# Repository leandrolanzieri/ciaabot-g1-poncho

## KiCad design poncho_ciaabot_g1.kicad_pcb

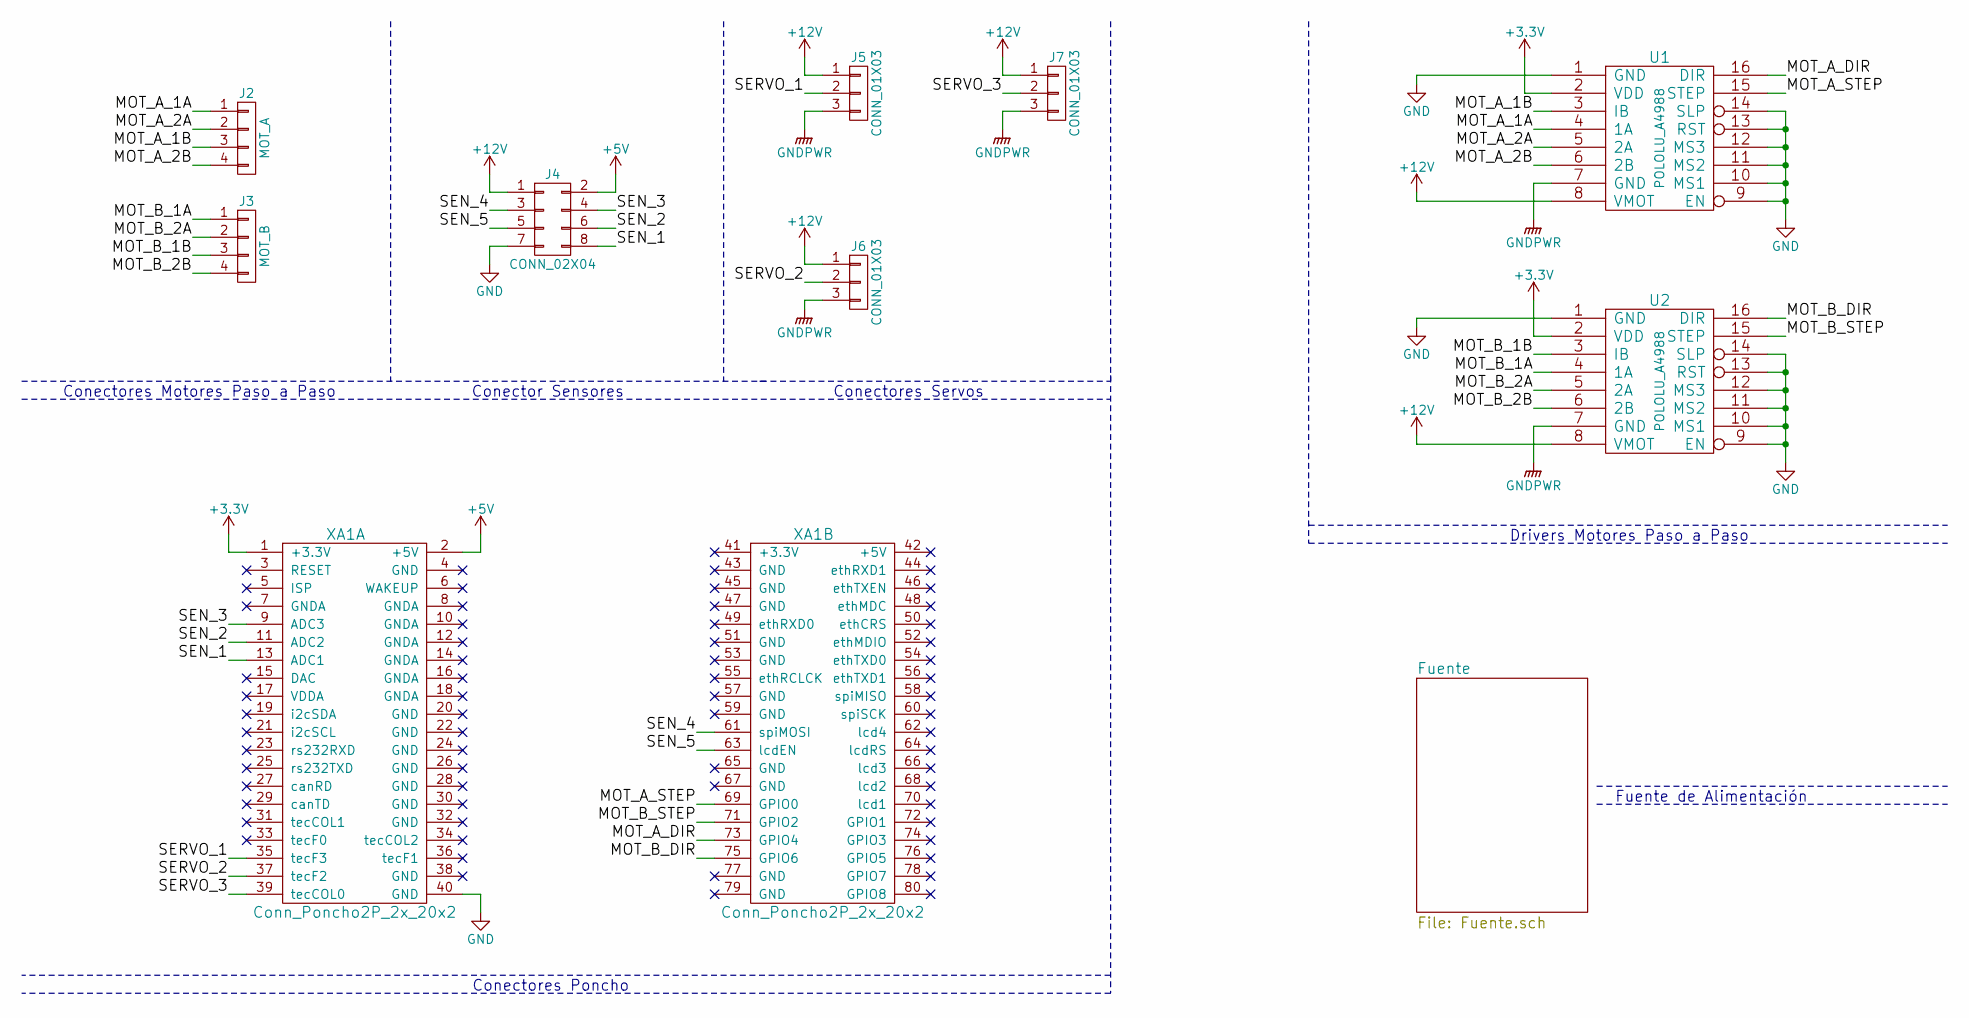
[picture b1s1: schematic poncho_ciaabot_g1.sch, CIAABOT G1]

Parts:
J2: MOT_A; Pin_Header_Straight_1x04_Pitch2.54mm; Digikey# S7002-ND
J3: MOT_B; Pin_Header_Straight_1x04_Pitch2.54mm; Digikey# S7002-ND
J4: CONN_02X04; Pin_Header_Straight_2x04_Pitch2.54mm; Digikey# S7072-ND
J5, J6, J7: CONN_01X03; Pin_Header_Straight_1x03_Pitch2.54mm; Digikey# S7001-ND
U1, U2: POLOLU_A4988; SWDIP8_.6W
XA1: Conn_Poncho2P_2x_20x2; Conn_Poncho_Completo; Digikey# 952-1897-ND

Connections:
+3V3: U1.2 (VDD), U2.2 (VDD), XA1.1 (+3.3V)
+5V: J4.2, XA1.2 (+5V)
+12V: J4.1, J5.1, J6.1, J7.1, U1.8 (VMOT), U2.8 (VMOT); also elsewhere on the board
/MOT_A_1A: J2.1, U1.4 (1A)
/MOT_A_1B: J2.3, U1.3 (IB)
/MOT_A_2A: J2.2, U1.5 (2A)
/MOT_A_2B: J2.4, U1.6 (2B)
/MOT_A_DIR: U1.16 (DIR), XA1.73 (GPIO4)
/MOT_A_STEP: U1.15 (STEP), XA1.69 (GPIO0)
/MOT_B_1A: J3.1, U2.4 (1A)
/MOT_B_1B: J3.3, U2.3 (IB)
/MOT_B_2A: J3.2, U2.5 (2A)
/MOT_B_2B: J3.4, U2.6 (2B)
/MOT_B_DIR: U2.16 (DIR), XA1.75 (GPIO6)
/MOT_B_STEP: U2.15 (STEP), XA1.71 (GPIO2)
/SEN_1: J4.8, XA1.13 (ADC1)
/SEN_2: J4.6, XA1.11 (ADC2)
/SEN_3: J4.4, XA1.9 (ADC3)
/SEN_4: J4.3, XA1.61 (spiMOSI)
/SEN_5: J4.5, XA1.63 (lcdEN)
/SERVO_1: J5.2, XA1.35 (tecF3)
/SERVO_2: J6.2, XA1.37 (tecF2)
/SERVO_3: J7.2, XA1.39 (tecCOL0)
GND: J4.7, J5.3, J6.3, J7.3, U1.1 (GND), U1.7 (GND), U1.9 (EN), U1.10 (MS1), U1.11 (MS2), U1.12 (MS3), U1.13 (RST), U1.14 (SLP), U2.1 (GND), U2.7 (GND), U2.9 (EN), U2.10 (MS1), U2.11 (MS2), U2.12 (MS3), U2.13 (RST), U2.14 (SLP), XA1.40 (GND); also elsewhere on the board

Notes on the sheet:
Conector Sensores
Conectores Servos
Drivers Motores Paso a Paso
Conectores Motores Paso a Paso
Conectores Poncho
Fuente de Alimentación

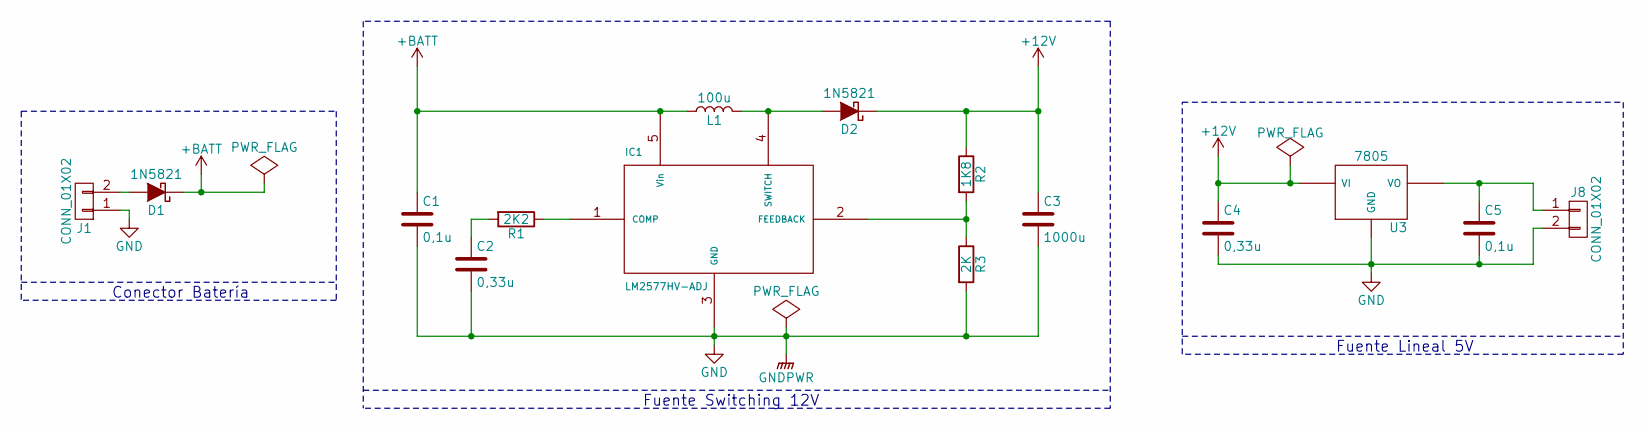
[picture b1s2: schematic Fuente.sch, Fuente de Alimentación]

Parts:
C1, C5: 0,1u; C_Disc_D3.0mm_W2.0mm_P2.50mm; Digikey# 493-10498-3-ND
C2, C4: 0,33u; C_Disc_D3.0mm_W2.0mm_P2.50mm; Digikey# 493-10258-3-ND
C3: 1000u; C_Disc_D3.0mm_W2.0mm_P2.50mm; Digikey# 1189-1583-3-ND
D1, D2: 1N5821; D_A-405_P7.62mm_Horizontal; Digikey# 1N5821FSCT-ND
IC1: LM2577HV-ADJ; TO-220-5_Vertical; Digikey# LM2577T-ADJ/NOPB-ND
J1: CONN_01X02; bornier2; Digikey# 277-1667-ND
J8: CONN_01X02; Pin_Header_Straight_2x01_Pitch2.54mm; Digikey# A1921-ND
L1: 100u; Choke_Toroid_horizontal_Diameter3-5mm_Amidon-T12; Digikey# M8354-ND
R1: 2K2; R_Axial_DIN0204_L3.6mm_D1.6mm_P5.08mm_Horizontal; Digikey# S2.2KQTR-ND
R2: 1K8; R_Axial_DIN0204_L3.6mm_D1.6mm_P5.08mm_Horizontal; Digikey# S1.8KQTR-ND
R3: 2K; R_Axial_DIN0204_L3.6mm_D1.6mm_P5.08mm_Horizontal; Digikey# S2KQTR-ND
U3: 7805; TO-220-3_Vertical; Digikey# LM7805CT-ND

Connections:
+12V: C3.1, C4.1, D2.1 (K), R2.1, U3.VI; also elsewhere on the board
+BATT: C1.1, D1.1 (K), IC1.5 (Vin), L1.1
GND: C1.2, C2.2, C3.2, C4.2, C5.2, IC1.3 (GND), J1.1, J8.2, R3.2, U3.GND; also elsewhere on the board
unnamed: C2.1, R1.2
unnamed: C5.1, J8.1, U3.VO
unnamed: D1.2 (A), J1.2
unnamed: D2.2 (A), IC1.4 (SWITCH), L1.2
unnamed: IC1.1 (COMP), R1.1
unnamed: IC1.2 (FEEDBACK), R2.2, R3.1

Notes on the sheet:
Conector Batería
Fuente Switching 12V
Fuente Lineal 5V

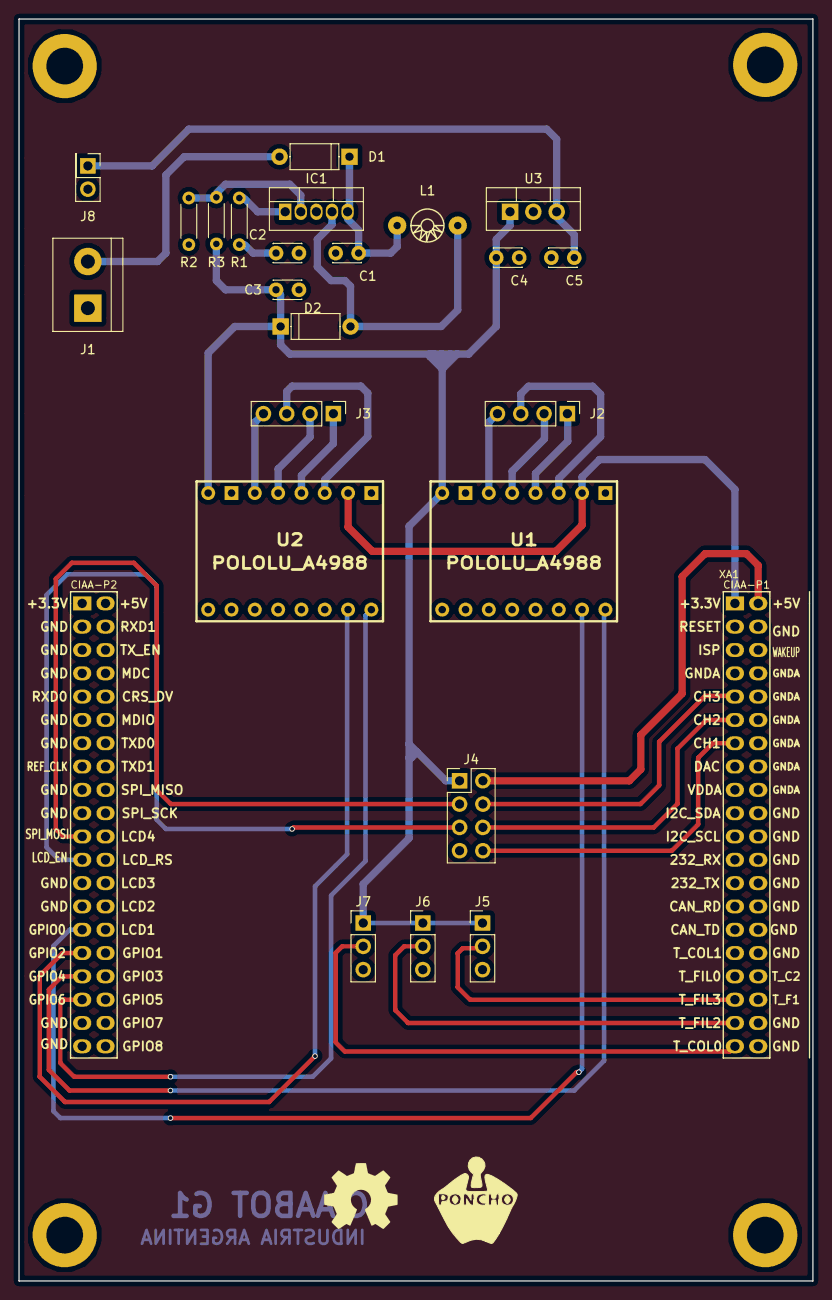
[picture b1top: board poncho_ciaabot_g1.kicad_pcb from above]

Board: 2 copper layers, 86.5 x 137.5 mm, 25 parts (0 on the bottom side), 31 nets.

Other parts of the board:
G101: Logo_OSHWA

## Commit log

2017-05-11 Archivos iniciales y primer esquematico
2017-10-18 Reestructuracion de hojas de esquematico.
2017-10-18 Se agregan bibliotecas de esquematico y huellas
2017-10-18 Se agrega biblioteca poncho esqueleto faltante
2017-10-18 Se agregan codigos de DigiKey
2017-10-25 Se aplican las primeras correciones del profesor sobre esquematico
2017-11-05 Primera version del PCB
2017-11-05 Se agrega borde PCB
2017-11-12 Se agregan modelos 3D conectores, cap. y diodos
2017-11-19 Se agrega area de cobre en capa superior
